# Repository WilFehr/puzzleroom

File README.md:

# puzzleroom
Inspired by a DND puzzle room where the solution is to be patient and let the timer tick to zero

# what is in this repo?
this repo was started quite late in the development process so was created with the some of the files that will be in the final project

# next step
This project is complete!

# purpose 
the purpose of this project was to:
- gain practial circuit board development experience using KiCad,
- gain more 3D modeling experience using Solidworks
- gain familiarity with the Arduino IDE

# key take aways
I've learned many things from this experience, such as:
- the importance of test points in PCB manufacturing;
  - at some point one LED blew out and it took me a while to figure out that that was the issue and not some other hardware/software issue, having easy access to key circuit points would have made this much faster
- the iterative design nature in engineering;
  - I had many test breadboard circuits before I set up the schematic in KiCad
  - I had many test prints of the base of the housing before I had a design that worked and I was satisfied with.

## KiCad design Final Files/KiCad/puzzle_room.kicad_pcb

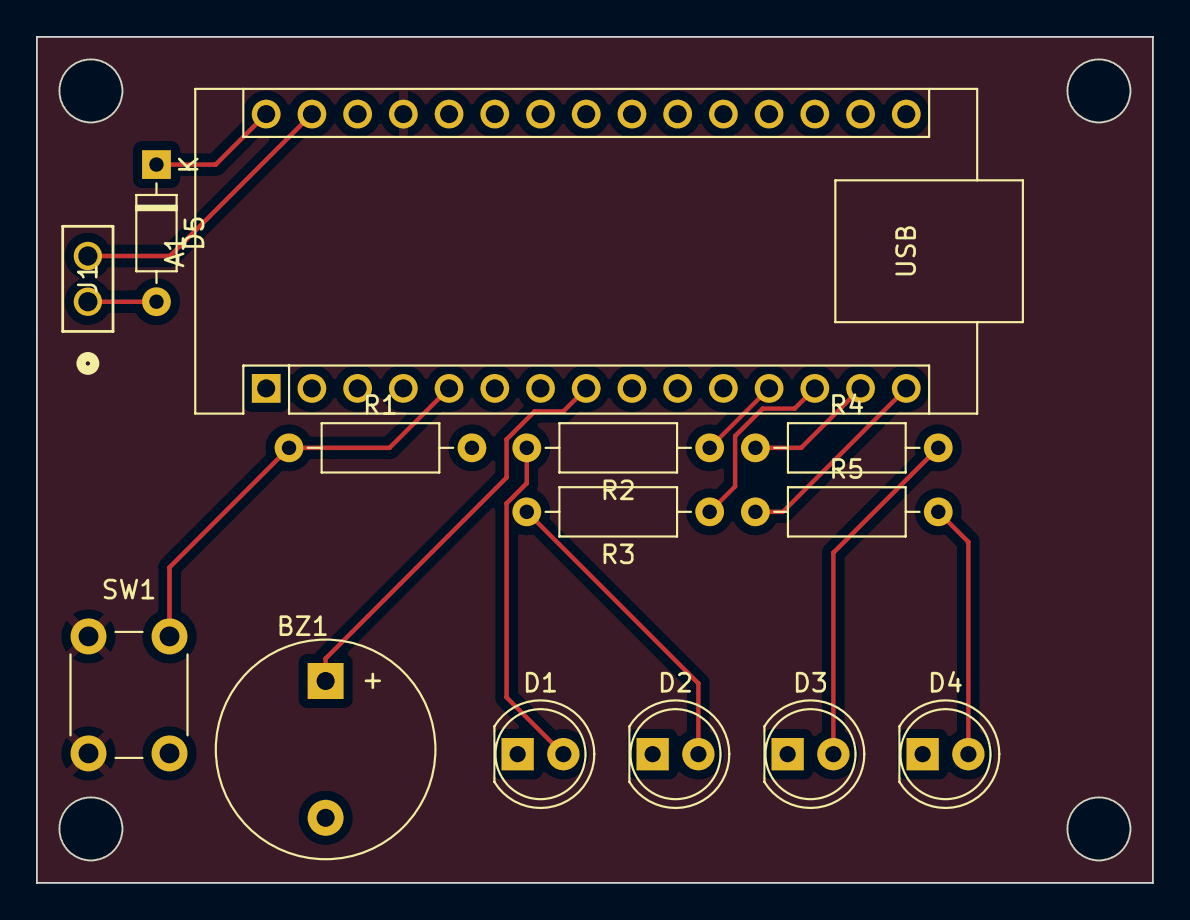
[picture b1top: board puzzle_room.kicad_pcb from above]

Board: 2 copper layers, 62.0 x 47.0 mm, 14 parts (0 on the bottom side), 14 nets.

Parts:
A1: Arduino_Nano_v2.x; Arduino_Nano
BZ1: Buzzer; Buzzer_12x9.5RM7.6
D1, D2, D3, D4: LD271; LED_D5.0mm_IRGrey
D5: 1N914; D_DO-35_SOD27_P7.62mm_Horizontal
J1: PPTC021LFBN-RC; CONN2_LFBN-RC_SUL
R1: 10k; R_Axial_DIN0207_L6.3mm_D2.5mm_P10.16mm_Horizontal
R2, R3, R4, R5: 330; R_Axial_DIN0207_L6.3mm_D2.5mm_P10.16mm_Horizontal
SW1: SW_Push; SW_PUSH_6mm

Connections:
9v_in: D5.2 (A), J1.1
+5V: A1.27 (+5V), SW1.1
GND: A1.4 (GND), A1.29 (GND), BZ1.2 (+), D1.1 (K), D2.1 (K), D3.1 (K), D4.1 (K), J1.2, R1.2
Green: A1.15 (D12), R5.1
unnamed: A1.30 (VIN), D5.1 (K)
unnamed: D1.2 (A), R2.2
unnamed: D2.2 (A), R3.2
unnamed: D3.2 (A), R4.2
unnamed: D4.2 (A), R5.2
Red1: A1.13 (D10), R3.1
Red2: A1.12 (D9), R2.1
Speaker: A1.8 (D5), BZ1.1 (-)
Yellow: A1.14 (D11), R4.1
button: A1.5 (D2), R1.1, SW1.2

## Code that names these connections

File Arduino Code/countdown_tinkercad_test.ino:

// C++ code
//
#define toggle(x) digitalWrite(x, !digitalRead(x));

//const
const int green = 12;
const int yellow = 11;
const int red1 = 10;
const int red2 = 9;
const int button = 2;
const int speaker = 5;

volatile int state = 0;

//debounce code
unsigned long int last_debounce_time = 0;
unsigned long int debounce_delay = 50;//increase if flickers

/*
unsigned long int current_debounce_time = millis();
if ((current_debounce_time - last_debounce_time) > debounce_delay){
	//stuff in here
}
last_debounce_time = current_debounce_time;
*/


const int maxtime = 30;//max time in sec
int max_ms = maxtime*1000; // max time in ms
int max_iter = maxtime*100;
unsigned long int start_of_timer = millis();//start of program


void setup()
{
   pinMode(green, OUTPUT);
  pinMode(yellow, OUTPUT);
  pinMode(red1, OUTPUT);
  pinMode(speaker, OUTPUT);
  pinMode(red2, OUTPUT);
  pinMode(button, INPUT_PULLUP);
  attachInterrupt(digitalPinToInterrupt(button), next, RISING);

}

//change value represents time between toggles.
int place_holder = 1;

void loop()
{
  switch(state){
    case 0:
    digitalWrite(green, 1);
    digitalWrite(yellow, 0);
    digitalWrite(red2, 0);
    digitalWrite(red1, 0);
    digitalWrite(speaker, 1);
    state = 1;
    //green
      //0.33*max_iter
      for (int t = 0; t < 10; t++){
        //delay between toggles
        for(int i = 0; i < max_iter*0.033; i++){//10 ms per iteration
          delay(10);
          if(state == 0)
            break;
        }
        if(state == 0)
            break;
        //toggle
        toggle(green);
        toggle(speaker);
      //
      }//end of green
      if(state == 0)
            break;
      //turn green off
      digitalWrite(green, 0);
      digitalWrite(speaker, 0);


    //yellow
      //0.27*max_iter
      for (int t = 0; t < 10; t++){
        //toggle
        toggle(yellow);
        toggle(speaker);
        //delay between toggles
        for(int i = 0; i < max_iter*0.027; i++){//10 ms per iteration
          delay(10);
          if(state == 0)
            break;
        }
        if(state == 0)
            break;
        

      //
      }//end of yellow
      if(state == 0)
            break;
      //turn yellow off
      digitalWrite(yellow, 0);
      digitalWrite(speaker, 0);

    //red1
      //0.20*max_iter
      for (int t = 0; t < 10; t++){
        //toggle
        toggle(red1);
        toggle(speaker);
        //delay between toggles
        for(int i = 0; i < max_iter*0.02; i++){//10 ms per iteration
          delay(10);
          if(state == 0)
            break;
        }
        if(state == 0)
            break;
        

      //
      }//end of red1
      if(state == 0)
            break;
      //turn red1 off
      digitalWrite(red1, 0);
      digitalWrite(speaker, 0);

    //red2
      //0.13*max_iter
      for (int t = 0; t < 10; t++){
        //toggle
        toggle(red2);
        toggle(speaker);
        //delay between toggles
        for(int i = 0; i < max_iter*0.013; i++){//10 ms per iteration
          delay(10);
          if(state == 0)
            break;
        }
        if(state == 0)
            break;
        

      //
      }//end of red2
      if(state == 0)
            break;
      //turn red2 off
      //digitalWrite(red2, 0);

    //red flash
      //0.07*max_iter
      for (int t = 0; t < 10; t++){//number of toggles
        //toggle
        toggle(red2);
        toggle(red1);
        toggle(speaker);
        //delay between toggles
        for(int i = 0; i < max_iter*0.007; i++){//10 ms per iteration
          delay(10);
          if(state == 0)
            break;
        }
        if(state == 0)
            break;
      //
      }//end of red flash
      if(state == 0)
            break;
      //turn red off
      digitalWrite(red2, 0);
      digitalWrite(red1, 0);
      digitalWrite(speaker, 0);

    int end_cycle1 [8] = { 12, 12, 11, 11, 10, 10, 9, 9};
    int end_cycle2 [8] = { 12, 11, 10, 9, 12, 11, 10, 9};

    //celebration
    for (int h = 0; h < 3; h++){
      for (int k = 0; k < 8; k++){//go through end cycle 1
        for(int i = 0; i < max_iter*0.01; i++){//10 ms per iteration
          delay(10);
          if(state == 0)
            break;
        }
        if(state == 0)
            break;
        //toggle
        toggle(end_cycle1[k]);
      }//end of celebration cycle 1
      if(state == 0)
        break;    
    }
    if(state == 0)
      break;

    //celebration
    for (int h = 0; h < 3; h++){
      for (int k = 0; k < 8; k++){//go through end cycle 1
        for(int i = 0; i < max_iter*0.01; i++){//10 ms per iteration
          delay(10);
          if(state == 0)
            break;
        }
        if(state == 0)
            break;
        //toggle
        toggle(end_cycle2[k]);
      }//end of celebration cycle 1
      if(state == 0)
        break;    
    }
    if(state == 0)
      break;


    default:
      //


      digitalWrite(green, 1);
      digitalWrite(yellow, 1);
      digitalWrite(red2, 1);
      digitalWrite(red1, 1);
      break;
  }
}

void next(){
  unsigned long int current_debounce_time = millis();
  if ((current_debounce_time - last_debounce_time) > debounce_delay){
      //stuff in here
    state = 0;
  }
  last_debounce_time = current_debounce_time;
};

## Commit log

2025-03-24 updating the github with the project so far
2025-03-25 starting the lid
2025-03-26 lid fit test files
    checking the fit of the LEDs in the lid and first draft of the locking mechanism
2025-03-26 the lid draft 1
    the first complete draft of the lid
2025-03-31 finalized the housing design and starting project wrap up
    finished the housing designs and am starting the process of collecting the final versions of the all the files, making the solidworks assembly and drawings.
